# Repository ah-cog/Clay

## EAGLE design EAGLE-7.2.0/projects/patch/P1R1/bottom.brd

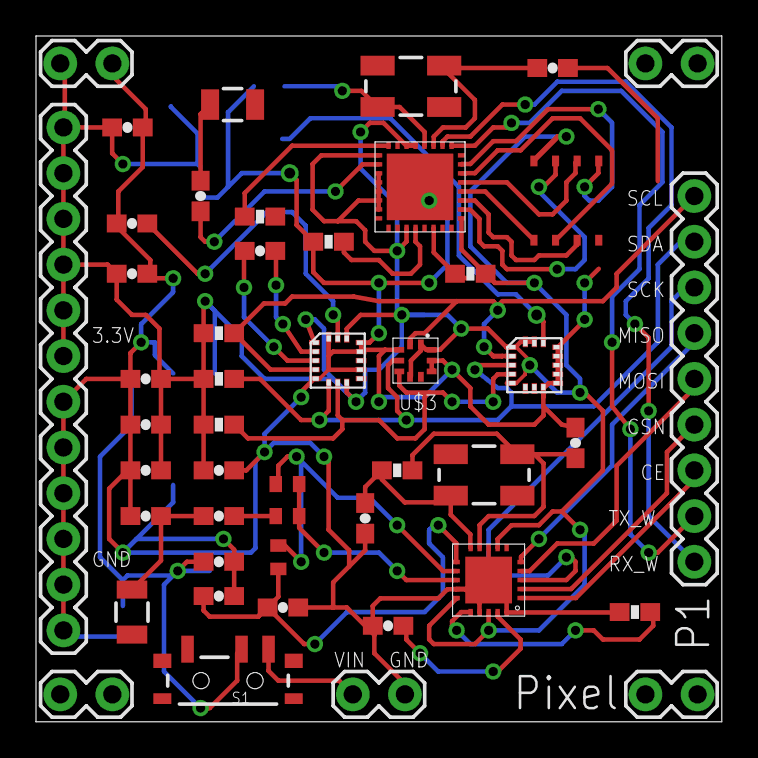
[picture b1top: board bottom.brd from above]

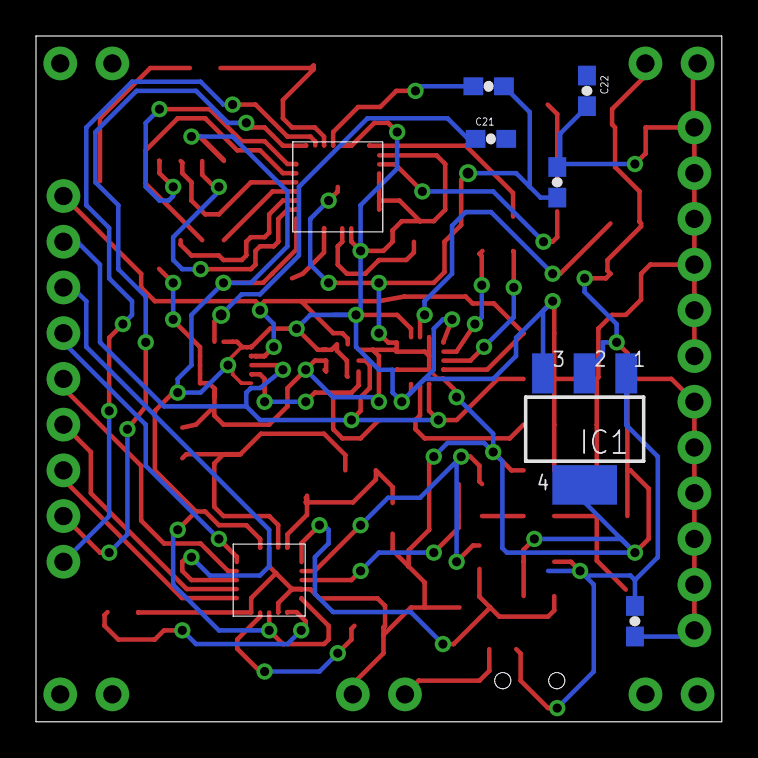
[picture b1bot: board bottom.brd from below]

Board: 2 copper layers, 38.1 x 38.1 mm, 53 parts (6 on the bottom side), 40 nets.

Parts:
C1, C23: 15 pF; 0603-CAP
C2, C8, C10, C15, C20: .1 uF; 0603-CAP
C3: 5.6 pF; 0603-CAP
C4, C11: 4.7 uF; 0603-CAP
C5: .22 uF; 0603-CAP
C6: 10 uF; 0603-CAP
C7, C19, C22: 1 uF; 0603-CAP
C9, C14: 22 pF; 0603-CAP
C12: 1.0 pF; 0603-CAP
C13: 1.5 pF; 0603-CAP
C16: 4.7 pF; 0603-CAP
C17: 2.2 nF; 0603-CAP
C18: 33 nF; 0603-CAP
C21: 10 nF; 0603-CAP
IC1: LM2936MP-3.3; SOT223
JP1, JP2, JP5, JP6, JP7: 1X02_LOCK
JP3: 1X09
JP4: 1X12
L1: 8.2 nH; C0402
L2: 3.9 nH; C0402
L3: 2.7 nH; C0402
LSM303D: LSM303D; LGA16L
MESH: NRF24L01; QFN20(4X4)
R1, R2, R3: 12k; 0603-RES
R4, R5, R6: 10k; 0603-RES
R7: 1M; 0603-RES
R8: 22k; 0603-RES
S1: SWITCH-SPST-SMD-A
U$1, U$5: ANTENNA2SMD; ANTENNA-CHIP2
U$2: 25Q40; SOP8
U$3: LPS25H
U$4: L3GD20H; LGA16L
WIFI: ESP8266EX; QFN32
Y1, Y2: 16 Mhz; CRYSTAL-SMD-5X3

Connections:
CE: JP3.3, MESH.1
CSN: JP3.4, MESH.2
GND: C1.2, C2.2, C4.2, C6.2, C7.2, C8.2, C9.2, C10.2, C11.2, C12.2, C14.2, C15.2, C16.2, C17.2, C18.1, C19.2, C20.2, C22.1, C23.2, IC1.2, IC1.4, JP1.2, JP4.1, JP4.2, JP4.3, JP4.4, JP4.5, JP4.6, JP6.2, LSM303D.P$5, LSM303D.P$10, LSM303D.P$12, LSM303D.P$13, LSM303D.P$16, MESH.8, MESH.14, MESH.17, MESH.20, R2.1, R8.2, U$2.4, U$3.3, U$3.8, U$3.9, U$4.P$8, U$4.P$9, U$4.P$10, U$4.P$11, U$4.P$12, U$4.P$13, WIFI.GND
MISO: JP3.6, MESH.5
MOSI: JP3.5, MESH.4
unnamed: C3.1, U$1.FEED
unnamed: R3.1, WIFI.GPIO2/14
unnamed: R2.2, WIFI.MTCK/12
unnamed: L1.2, L3.1, MESH.12
unnamed: C13.1, L2.2
unnamed: C12.1, C13.2, U$5.FEED
unnamed: C3.2, WIFI.LNA/2
unnamed: C9.1, MESH.9, R7.1, Y2.1
unnamed: C14.1, MESH.10, R7.2, Y2.3
unnamed: C16.1, C17.1, L3.2, MESH.11
unnamed: L1.1, L2.1, MESH.13
unnamed: C21.1, U$4.P$14
unnamed: MESH.16, R8.1
unnamed: C18.2, MESH.19
unnamed: C5.2, LSM303D.P$2
unnamed: C4.1, LSM303D.P$15
RST: R1.1, WIFI.EXT_RSTB/32
RX_W: JP3.1, WIFI.U0TXD/26
SCK: JP3.7, MESH.3
SCL: JP3.9, LSM303D.P$4, R4.2, U$3.2, U$4.P$2
SD-CLK: U$2.6, WIFI.SD_CLK/21
SD-CMD: U$2.1, WIFI.SD_CMD/20
SD-D0: U$2.2, WIFI.SD_DATA_0/22
SD-D1: U$2.5, WIFI.SD_DATA_1/23
SD-D2: U$2.7, WIFI.SD_DATA_2/18
SD-D3: U$2.3, WIFI.SD_DATA_3/19
SDA: JP3.8, LSM303D.P$6, R5.2, U$3.4, U$4.P$3
SDO: LSM303D.P$7, R6.2, U$3.5, U$4.P$4
SETP: C5.1, LSM303D.P$3
TX_W: JP3.2, WIFI.U0RXD/25
VDD: C2.1, C6.1, C7.1, C8.1, C10.1, C11.1, C20.1, C22.2, IC1.3, JP1.1, JP4.7, JP4.8, JP4.9, JP4.10, JP4.11, JP4.12, LSM303D.P$1, LSM303D.P$8, LSM303D.P$14, MESH.7, MESH.15, MESH.18, R3.2, R4.1, R5.1, R6.1, U$2.8, U$3.1, U$3.6, U$3.10, U$4.P$1, U$4.P$5, U$4.P$15, U$4.P$16, WIFI.CHIP_EN/7, WIFI.VDD3P3/3, WIFI.VDD3P3/4, WIFI.VDDA/1, WIFI.VDDA/30, WIFI.VDDD/29, WIFI.VDDPST/11, WIFI.VDDPST/17
VIN: JP6.1, S1.1
VRAW: C15.1, C19.1, IC1.1, S1.2
XTAL_IN: C23.1, WIFI.XTAL_IN/28, Y1.3
XTAL_OUT: C1.1, WIFI.XTAL_OUT/27, Y1.1

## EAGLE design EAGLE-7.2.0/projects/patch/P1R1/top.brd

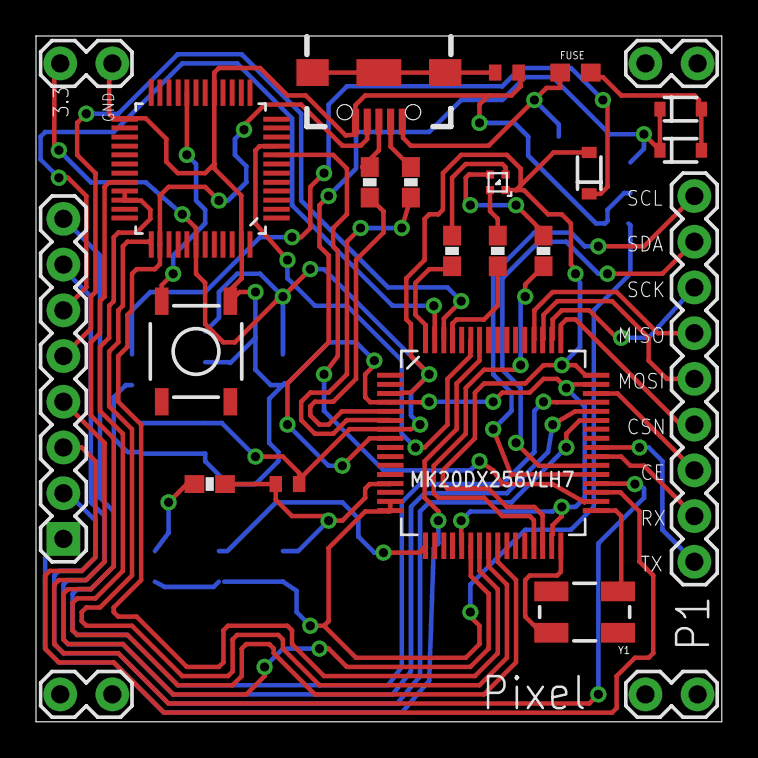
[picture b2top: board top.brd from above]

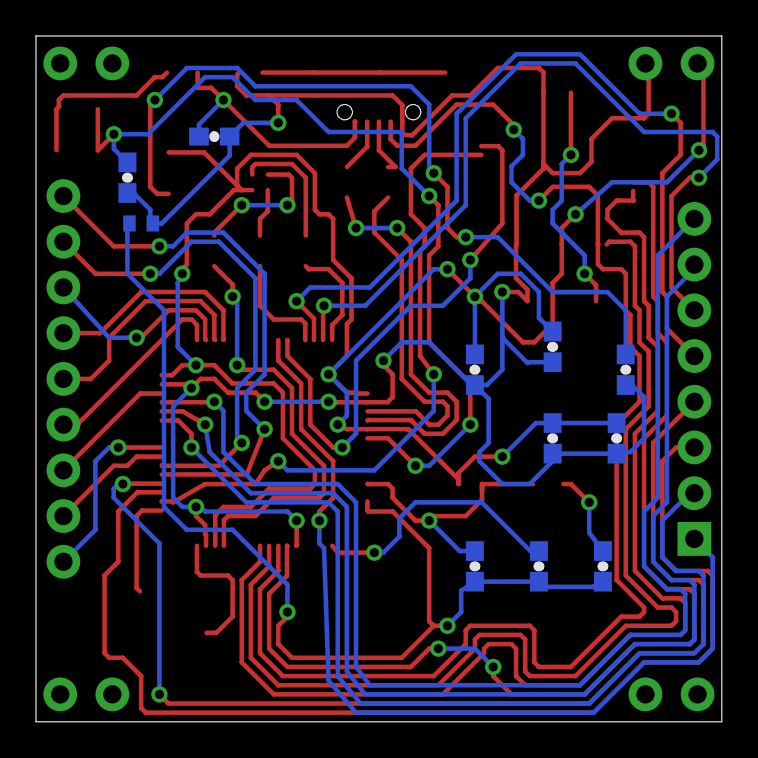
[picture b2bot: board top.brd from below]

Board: 2 copper layers, 38.1 x 38.1 mm, 35 parts (11 on the bottom side), 47 nets.

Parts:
C1, C2, C3, C4, C6, C7, C8, C9, C10: .1 uF; 0603-CAP
C5: 2.2 uF; 0603-CAP
D1, D2, D3: 1A; SOD-323
D4: SML-LX0404SIUPGUSB; 1MM_SQ_4PAD
FERRITE1, FERRITE2, FERRITE3: BLM15HB121SN1; 0402
FUSE: PTC0603; 0603
GPIO: 1X08
JP1, JP2, JP5, JP6: 1X02_LOCK
JP3: USB-B-MICRO-SMD_V03
JP4: 1X09
R1, R2: 33; 0603-RES
R3, R4, R5: 330; 0603-RES
R6: 470; 0603-RES
S1: SWITCH-MOMENTARY-2SMD; TACTILE-SWITCH-SMD
U$1: MINI54TANDEFAULT; QFP50P900X900X160-48N
U$2: MK20DX256VLH7; QFP50P1200X1200X160-64N
Y1: 16 MHz; CRYSTAL-SMD-5X3

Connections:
3.3V: C4.1, C5.1, C6.1, C8.1, D3.A, D4.1, FERRITE2.1, JP1.1, U$1.42, U$2.3, U$2.7, U$2.30, U$2.48
AGND: C1.2, C2.2, C3.2, FERRITE3.2, U$2.15, U$2.16
CE: JP4.3, U$2.46
D+: JP3.D+1, R1.1
D-: JP3.D-1, R2.1
GND-ISO: C4.2, C5.2, C6.2, C7.2, C8.2, C9.1, C10.1, FERRITE1.1, FERRITE3.1, JP1.2, JP3.GND1, S1.1, U$1.17, U$1.25, U$1.47, U$2.4, U$2.21, U$2.31, U$2.47
unnamed: C2.1, U$2.17
unnamed: C9.2, D1.C, D2.C, U$2.8
unnamed: C1.1, FERRITE2.2, R6.1, U$2.13
unnamed: C3.1, R6.2
unnamed: FERRITE1.2, JP3.SHIELD1, JP3.SHIELD2, JP3.SHIELD3
unnamed: S1.3, U$1.20
unnamed: C7.1, D3.C
unnamed: U$1.8, U$2.34
unnamed: JP3.ID1, U$1.38, U$2.23
unnamed: U$1.33, U$1.34, U$2.25
unnamed: U$1.32, U$2.22
unnamed: U$1.37, U$2.24
unnamed: U$1.9, U$2.59
unnamed: R1.2, U$2.5
unnamed: R2.2, U$2.6
unnamed: JP4.4, U$2.49
unnamed: U$2.32, Y1.3
unnamed: U$2.33, Y1.1
unnamed: JP4.5, U$2.51
unnamed: JP4.6, U$2.52
unnamed: GPIO.1, U$2.58
unnamed: GPIO.2, U$2.43
unnamed: GPIO.3, U$2.35
unnamed: D4.3, R5.2
unnamed: D4.4, R3.2
unnamed: D4.2, R4.2
unnamed: GPIO.4, U$2.36
unnamed: GPIO.5, U$2.62
unnamed: GPIO.6, U$2.63
unnamed: GPIO.7, U$2.44
unnamed: GPIO.8, U$2.45
unnamed: R3.1, U$2.64
unnamed: R5.1, U$2.29
unnamed: C10.2, FUSE.1, JP3.VBUS1
unnamed: R4.1, U$2.61
SCK: JP4.7, U$2.50
SCL_T: JP4.9, U$2.37
SDA_T: JP4.8, U$2.38
T_RX: JP4.2, U$2.39
T_TX: JP4.1, U$2.40
VIN: D1.A, D2.A, FUSE.2

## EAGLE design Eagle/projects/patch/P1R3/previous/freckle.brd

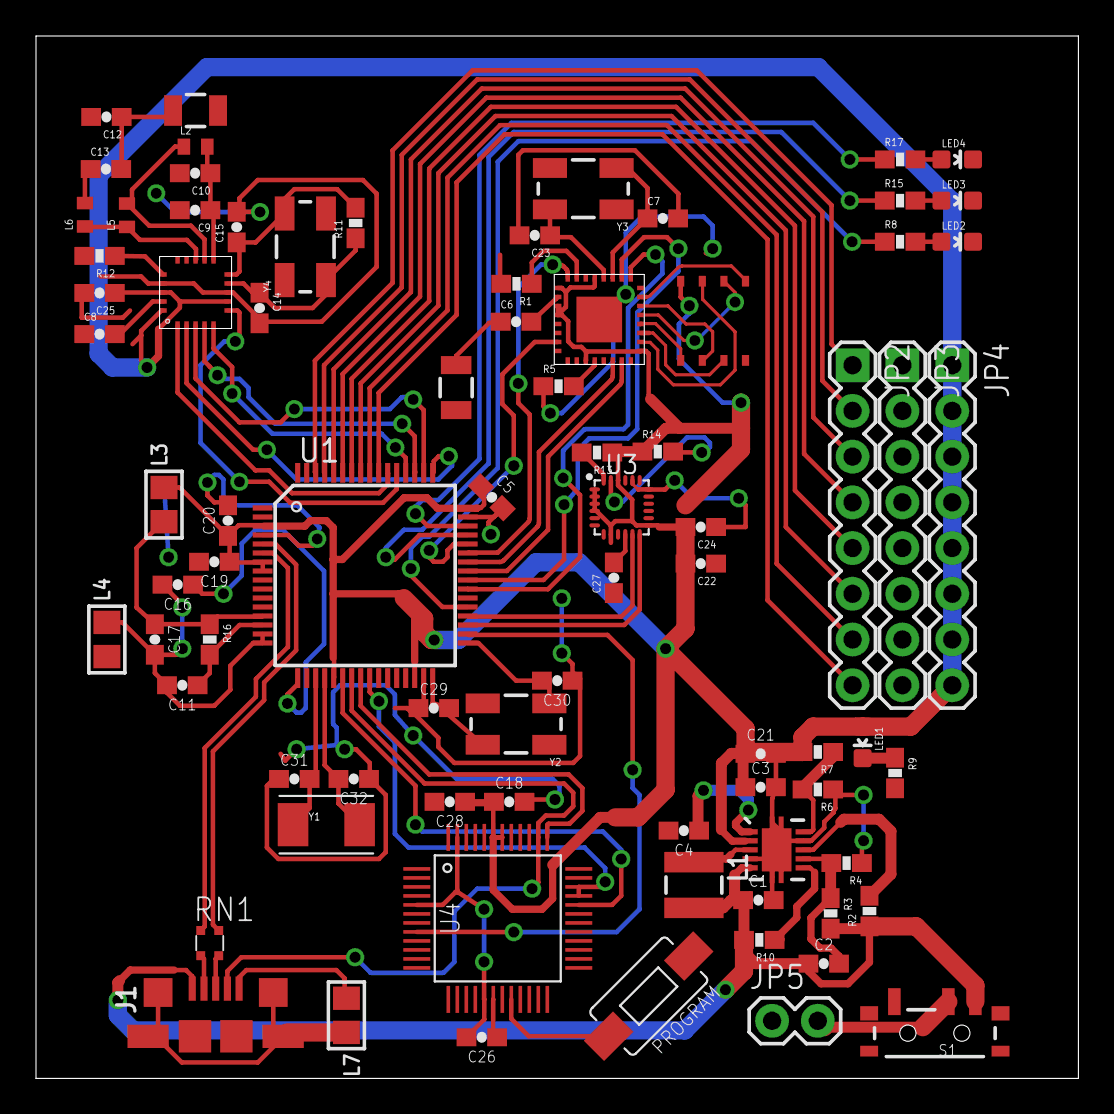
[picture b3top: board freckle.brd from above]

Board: 2 copper layers, 57.9 x 57.9 mm, 81 parts (0 on the bottom side), 83 nets.

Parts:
C1: 10uF; 0603-CAP
C2, C4, C5, C11, C16, C18, C19, C21, C26, C28: 0.1uF; 0603-CAP
C3: 22uF; 0603-CAP
C6: 5.6 pF; 0603-CAP
C7, C23: 15 pF; 0603-CAP
C8: 33 nF; 0603-CAP
C9: 2.2 nF; 0603-CAP
C10: 4.7 pF; 0603-CAP
C12: 1.0 pF; 0603-CAP
C13: 1.5 pF; 0603-CAP
C14, C15, C29, C30, C31, C32: 22 pF; 0603-CAP
C17, C20: 2.2uF; 0603-CAP
C22: 1 uF; 0603-CAP
C24, C25, C27: .1 uF; 0603-CAP
J1: 1981584-1
JP2, JP3, JP4: 1X08
JP5: 1X02
L1: 2.2uH, 2.1A; LPS3015
L2: 2.7 nH; C0402
L3, L4, L7: 600 Ohm/100 Mhz; 0805
L5: 8.2 nH; C0402
L6: 3.9 nH; C0402
LED1, LED2, LED3, LED4: LED-0603
PROGRAM: Program; TACTILE-SWITCH-1101NE
R1, R5: 12k; 0603-RES
R2: 10K; 0603-RES
R3: 2M; 0603-RES
R4, R6: 220K; 0603-RES
R7: 1.2M; 0603-RES
R8, R15, R17: 330; 0603-RES
R9, R16: 470; 0603-RES
R10: 1K; 0603-RES
R11: 1M; 0603-RES
R12: 22k; 0603-RES
R13, R14: 10k; 0603-RES
RN1: 33; EXB34V
S1: SWITCH-SPST-SMD-A
U1: MK20DX256VLH7
U2: TPS61200; QFN-10_PAD
U3: MPU-9250; QFN-24/3MM
U4: MINI54TAN
U$1, U$2: ANTENNA2SMD; ANTENNA-CHIP2
U$3: 25Q40; SOP8
U$4: NRF24L01; QFN20(4X4)
U$6: ESP8266EX; QFN32
Y1: 32.768KHz; CRYSTAL-TXC-7A
Y2: 16Mhz/8pF; CRYSTAL-SMD-5X3
Y3: 26 Mhz; CRYSTAL-SMD-5X3
Y4: 16 Mhz; CRYSTAL-SMD-5X3

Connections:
3.3V: C3.1, C5.1, C18.1, C19.1, C20.1, C21.1, C22.2, C24.2, C25.1, C28.1, JP4.1, JP4.2, JP4.3, JP4.4, JP4.5, JP4.6, JP4.7, JP4.8, L3.2, LED1.A, R7.2, R13.1, R14.1, U1.3, U1.7, U1.8, U1.21, U1.30, U1.48, U2.2, U3.1, U3.8, U3.13, U3.22, U4.42, U4.43, U$3.8, U$4.7, U$4.18, U$6.VDD3P3/3, U$6.VDD3P3/4, U$6.VDDA/1, U$6.VDDD/29, U$6.VDDPST/11, U$6.VDDPST/17
FB: R6.2, R7.1, U2.10
GND: C1.2, C3.2, C4.2, C5.2, C7.2, C8.1, C9.2, C10.2, C12.2, C14.2, C15.2, C18.2, C19.2, C20.2, C21.2, C22.1, C23.2, C24.1, C25.2, C26.2, C27.1, C28.2, C29.1, C30.1, C31.1, C32.1, J1.5, JP3.1, JP3.2, JP3.3, JP3.4, JP3.5, JP3.6, JP3.7, JP3.8, JP5.1, L4.1, L7.1, LED2.C, LED3.C, LED4.C, PROGRAM.P$1, R1.2, R4.1, R5.1, R6.1, R9.2, R12.2, U1.4, U1.31, U1.47, U2.4, U2.9, U2.11, U2.12, U2.13, U2.14, U2.15, U3.18, U3.20, U4.5, U4.17, U4.25, U4.47, U$3.4, U$4.8, U$4.17, U$4.20, U$6.GND
ID: J1.4, U1.23, U4.38
unnamed: LED1.C, R9.1
unnamed: L1.1, U2.3
unnamed: LED2.A, R8.2
unnamed: LED3.A, R15.2
unnamed: LED4.A, R17.2
unnamed: PROGRAM.P$2, U4.20
unnamed: C26.1, U4.18
unnamed: C6.2, U$6.LNA/2
unnamed: C6.1, U$1.FEED
unnamed: C14.1, R11.1, U$4.9, Y4.1
unnamed: C15.1, R11.2, U$4.10, Y4.3
unnamed: C9.1, C10.1, L2.2, U$4.11
unnamed: L5.1, L6.1, U$4.13
unnamed: C8.2, U$4.19
unnamed: L2.1, L5.2, U$4.12
unnamed: R12.1, U$4.16
unnamed: C13.1, L6.2
unnamed: C12.1, C13.2, U$2.FEED
unnamed: C29.2, U1.32, Y2.3
unnamed: C30.2, U1.33, Y2.1
unnamed: C31.2, U1.19, Y1.P$2
unnamed: C32.2, U1.20, Y1.P$1
unnamed: R5.2, U$6.MTCK/12
unnamed: C27.2, U3.10
unnamed: R1.1, U$6.RES12K/31
PS: R2.2, U2.8
PTA2: U1.24, U4.37
PTB0: U1.35, U3.12
PTB1: U1.36, U3.11
PTB2: R8.1, U1.37
PTB16: U1.39, U$6.U0RXD/25
PTB17: U1.40, U$6.U0TXD/26
PTB18: U1.41, U$6.GPIO0/15
PTB19: U1.42, U$6.GPIO2/14
PTC0: U1.43, U$6.EXT_RSTB/32
PTC1: U1.44, U$6.CHIP_EN/7
PTC2: R15.1, U1.45
PTC3: R17.1, U1.46
PTC4: U1.49, U$4.2
PTC5: U1.50, U$4.3
PTC6: U1.51, U$4.4
PTC7: U1.52, U$4.5
PTC8: U1.53, U$4.6
PTC9: U1.54, U$4.1
PTC10: JP2.8, U1.55
PTC11: JP2.7, U1.56
PTD0: JP2.6, U1.57
PTD1: JP2.5, U1.58
PTD2: JP2.4, U1.59
PTD3: JP2.3, U1.60
PTD4: JP2.2, U1.61
PTD5: JP2.1, U1.62
RESET_B: U1.34, U4.8
SCL: R14.2, U3.23
SD-CLK: U$3.6, U$6.SD_CLK/21
SD-CMD: U$3.1, U$6.SD_CMD/20
SD-D0: U$3.2, U$6.SD_DATA_0/22
SD-D1: U$3.5, U$6.SD_DATA_1/23
SD-D2: U$3.7, U$6.SD_DATA_2/18
SD-D3: U$3.3, U$6.SD_DATA_3/19
SDA: R13.2, U3.24
SOFTPOWER: R10.1, U2.6
SWD_CLK: U1.22, U4.32
SWD_DIO: U1.25, U4.33, U4.34
USB_CON_N: J1.2, RN1.1
USB_CON_P: J1.3, RN1.2
USB_D_N: RN1.4, U1.6
USB_D_P: RN1.3, U1.5
USB_SHIELD: J1.S1, J1.S2, J1.S3, J1.S4, L7.2
UVLO: C2.2, R3.1, R4.2, U2.7
VAUX: C4.1, U2.1
VCC: C1.1, C2.1, J1.1, L1.2, R2.1, R3.2, R10.2, S1.1, U2.5
VDDA: C17.1, L3.1, R16.1, U1.13
VRAW: JP5.2, S1.2
VREFH: C11.1, R16.2, U1.14
VREFL: C11.2, C16.2, C17.2, L4.2, U1.15, U1.16
VREF_OUT: C16.1, U1.17
XTAL_IN: C23.1, U$6.XTAL_IN/28, Y3.3
XTAL_OUT: C7.1, U$6.XTAL_OUT/27, Y3.1

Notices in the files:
parts and their libraries:
SparkFun-Capacitors: Licensing: Creative Commons ShareAlike 4.0 International - https://creativecommons.org/licenses/by-sa/4.0
con-usb: Copyright (C) 2008, Bob Starr
